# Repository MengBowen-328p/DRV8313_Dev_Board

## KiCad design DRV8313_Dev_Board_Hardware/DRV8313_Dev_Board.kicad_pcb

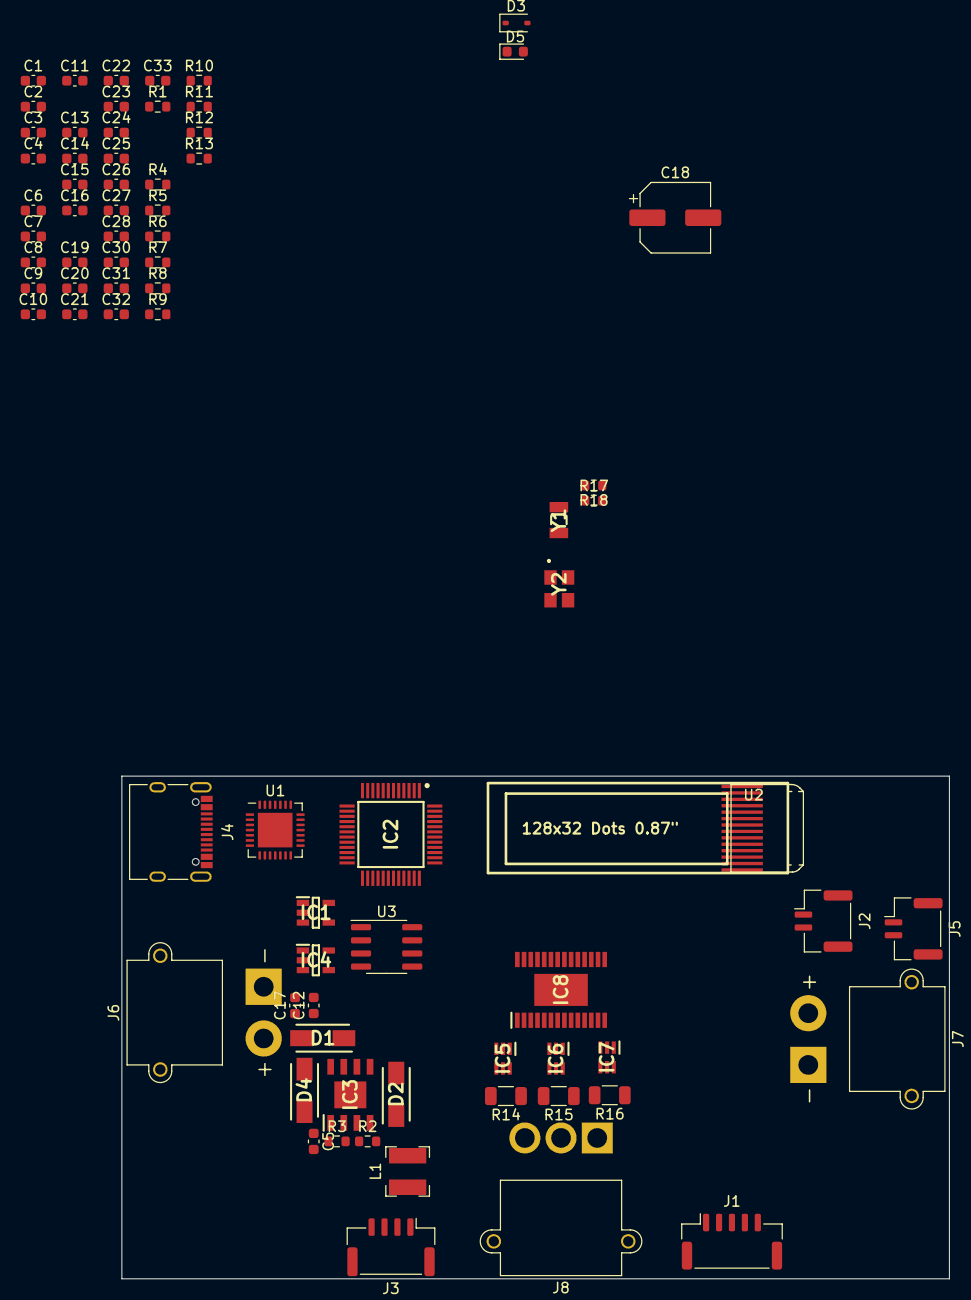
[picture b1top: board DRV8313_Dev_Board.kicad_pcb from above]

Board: 2 copper layers, 80.0 x 48.6 mm, 77 parts (0 on the bottom side), 65 nets, no tracks yet.

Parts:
C1, C5, C9, C10, C11, C13, C23, C26, C31: 0.1uF; C_0603_1608Metric
C2, C7, C15, C19, C27, C28: 1uF; C_0603_1608Metric
C3, C6, C16: 47pF; C_0603_1608Metric
C4: 47pf; C_0603_1608Metric
C8, C20: 0.01uF; C_0603_1608Metric
C12, C14, C17, C21, C22, C25: 4.7uF; C_0603_1608Metric
C18: 470uF; CP_Elec_6.3x5.7
C24: 2.2uF; C_0603_1608Metric
C30: 0.47uF; C_0603_1608Metric
C32: 0.01uF/60V; C_0603_1608Metric
C33: 0.1uF/16V; C_0603_1608Metric
D1, D2, D4: SS54; DIOM5126X245N
D3: 1N4148WS; D_SOD-323
D5: FAULT; LED_0603_1608Metric
IC1, IC4: LP2992IM5-3.3; SOT95P280X145-5N
IC2: STM32F103C8T6TR; QFP50P900X900X160-48N
IC3: TPS5450DDAR; SOIC127P600X170-9N
IC5, IC6, IC7: INA199A1DCKR; SOT65P210X110-6N
IC8: DRV8313PWP; SOP65P640X120-29N
J1: HALL_Sensor_Port; JST_GH_SM05B-GHS-TB_1x05-1MP_P1.25mm_Horizontal
J2: CAN_BUS_Port_IN; JST_GH_BM02B-GHS-TBT_1x02-1MP_P1.25mm_Vertical
J3: AS5600_Port; JST_GH_BM04B-GHS-TBT_1x04-1MP_P1.25mm_Vertical
J4: USB_C_Receptacle; USB_C_Receptacle_XKB_U262-16XN-4BVC11
J5: CAN_BUS_Port_OUT; JST_GH_BM02B-GHS-TBT_1x02-1MP_P1.25mm_Vertical
J6: DC_IN; AMASS_XT30PW-M_1x02_P2.50mm_Horizontal
J7: DC_OUT; AMASS_XT30PW-M_1x02_P2.50mm_Horizontal
J8: Conn_01x03_Socket; AMASS_MR30PW-M_1x03_P3.50mm_Horizontal
L1: 15uH; L_Bourns-SRN4018
R1, R2, R4: 10K; R_0603_1608Metric
R3: 3.16K; R_0603_1608Metric
R5, R6, R7, R8, R10: 4.7K; R_0603_1608Metric
R9: 560K; R_0603_1608Metric
R11, R12: 5K1; R_0603_1608Metric
R13: 4.99K; R_0603_1608Metric
R14, R15, R16: 500mR; R_1206_3216Metric
R17: 120R; R_0603_1608Metric
R18: 0R; R_0603_1608Metric
U1: CP2102N-Axx-xQFN28; QFN-28-1EP_5x5mm_P0.5mm_EP3.35x3.35mm
U2: 中景园_0.87寸OLED; 中景园0.87寸OLED
U3: SN65HVD232; SOIC-8_3.9x4.9mm_P1.27mm
Y1: 32.768KHZ_YST310S; 32768KHZYST310S
Y2: YSX321SL

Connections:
+3.3V: C7.1, C9.1, C10.1, C11.1, C13.1, C22.2, C23.2, C31.2, IC1.5 (OUT), IC2.1 (VBAT), IC2.9 (VDDA), IC2.24 (VDD_1), IC2.36 (VDD_2), IC2.48 (VDD_3), R1.2, R7.1, R8.1, R10.1, U2.5 (VBAT), U2.8 (VDD), U3.3 (VCC)
+5V: C2.1, C14.1, C15.1, C18.1, D3.1 (K), IC1.1 (IN), IC1.3 (ON/~OFF), IC4.1 (IN), IC4.3 (ON/~OFF), L1.2, R2.2, R4.2, U1.7 (VREGIN), U1.8 (VBUS)
/AS5600_SCL: J3.2, R8.2
/AS5600_SDA: J3.3, R10.2
/CAN_DN: J2.2, J5.2, R18.1, U3.6 (CANL)
/CAN_DP: J2.1, J5.1, R17.2, U3.7 (CANH)
/EN1: IC2.26 (PB13), IC8.26 (EN1)
/EN2: IC2.27 (PB14), IC8.24 (EN2)
/EN3: IC2.28 (PB15), IC8.22 (EN3)
/FAULT: D5.1 (K), IC2.39 (PB3), IC8.18 (NFAULT)
/IN1: IC2.29 (PA8), IC8.27 (IN1)
/IN2: IC2.30 (PA9), IC8.25 (IN2)
/IN3: IC2.31 (PA10), IC8.23 (IN3)
/ISense_U: IC2.12 (PA2), IC5.6 (OUT)
/ISense_V: IC2.11 (PA1), IC6.6 (OUT)
/ISense_W: IC2.10 (PA0-WKUP), IC7.6 (OUT)
/MCU_CAN_DN: IC2.32 (PA11), U3.4 (R)
/MCU_CAN_DP: IC2.33 (PA12), U3.1 (D)
/Motor0_U: IC5.4 (IN+), J8.3, R14.2
/Motor0_V: IC6.4 (IN+), J8.2, R15.2
/Motor0_W: IC7.4 (IN+), J8.1, R16.2
/OLED_SCL: IC2.45 (PB8), R5.2, U2.10 (SCL)
/OLED_SDA: IC2.46 (PB9), R6.2, U2.11 (SDA)
/OSC32_IN: C3.1, IC2.3 (PC14-OSC32_IN), Y1.2 (CRYSTAL_2)
/OSC32_OUT: C4.1, IC2.4 (PC15-OSC32_OUT), Y1.1
/OSC_IN: C6.1, IC2.5 (PD0-OSC_IN), Y2.1 (CRYSTAL_1)
/OSC_OUT: C16.2, IC2.6 (PD1-OSC_OUT), Y2.3 (CRYSTAL_2)
/OUT1: IC5.5 (IN-), IC8.5 (OUT1), R14.1
/OUT2: IC6.5 (IN-), IC8.8 (OUT2), R15.1
/OUT3: IC7.5 (IN-), IC8.9 (OUT3), R16.1
/RESET: IC2.41 (PB5), IC8.16 (NRESET)
/SLEEP: IC2.40 (PB4), IC8.17 (NSLEEP)
/USART1_RXD: IC2.43 (PB7), U1.26 (TXD)
/USART1_TXD: IC2.42 (PB6), U1.25 (RXD)
/USB_DN: J4.A7 (D-), J4.B7 (D-), U1.5 (D-)
/USB_DP: J4.A6 (D+), J4.B6 (D+), U1.4 (D+)
/V3P3_OUT: C30.2, IC5.3 (V+), IC6.3 (V+), IC7.3 (V+), IC8.15 (V3P3), R13.1
/VCC_OLED: R5.1, R6.1
/VCC_Sensor: C19.1, IC4.5 (OUT), J1.1, J3.1
GND: C1.2, C2.2, C3.2, C4.2, C6.2, C7.2, C8.2, C9.2, C10.2, C11.2, C12.2, C13.2, C14.2, C15.2, C16.1, C17.2, C18.2, C19.2, C20.2, C21.1, C22.1, C23.1, C24.1, C25.1, C26.1, C30.1, C31.1, D2.2 (A), D4.2 (A), IC1.2 (GND), IC2.8 (VSSA), IC2.23 (VSS_1), IC2.35 (VSS_2), IC2.47 (VSS_3), IC3.6 (GND), IC3.9 (EP), IC4.2 (GND), IC5.1 (REF), IC5.2 (GND), IC6.1 (REF), IC6.2 (GND), IC7.1 (REF), IC7.2 (GND), IC8.6 (PGND1), IC8.7 (PGND2), IC8.10 (PGND3), IC8.14 (GND_1), IC8.20 (GND_2), IC8.28 (GND_3), IC8.29 (POWERPAD), J1.5, J3.4, J4.A1 (GND), J4.A12 (GND), J4.B1 (GND), J4.B12 (GND), J4.S1 (SHIELD), J6.1, J7.1, R3.1, R9.1, R11.2, R12.2, U1.3 (GND), U1.29 (GND), U2.7 (VSS), U3.2 (GND), Y2.2 (GND_1), Y2.4 (GND_2)
unnamed: D1.1 (K), IC3.7 (VIN)
unnamed: C5.1, D2.1 (K), IC3.8 (PH), L1.1
unnamed: D3.2 (A), J4.A4 (VBUS), J4.A9 (VBUS), J4.B4 (VBUS), J4.B9 (VBUS)
unnamed: D5.2 (A), R13.2
unnamed: C8.1, IC1.4 (BYPASS)
unnamed: C1.1, IC2.7 (NRST), R1.1
unnamed: C5.2, IC3.1 (BOOT)
unnamed: IC3.4 (VSENSE), R2.1, R3.2
unnamed: C20.1, IC4.4 (BYPASS)
unnamed: C32.1, IC8.2 (CPH)
unnamed: C32.2, IC8.1 (CPL)
unnamed: C33.2, IC8.3 (VCP)
unnamed: J4.A5 (CC1), R11.1
unnamed: J4.B5 (CC2), R12.1
unnamed: R17.1, R18.2
unnamed: R4.1, U1.9 (~RST)
unnamed: R9.2, U2.12 (IREF)
unnamed: C21.2, R7.2, U2.9 (RES#)
unnamed: C25.2, C26.2, U2.14 (VCC)
unnamed: C24.2, U2.13 (VCOMH)
unnamed: C28.1, U2.4 (c1n)
unnamed: C28.2, U2.3 (c1p)
unnamed: C27.1, U2.2 (c2n)
unnamed: C27.2, U2.1 (c2p)
VCC: C12.1, C17.1, C33.1, D1.2 (A), D4.1 (K), IC8.4 (VM_1), IC8.11 (VM_2), J6.2, J7.2

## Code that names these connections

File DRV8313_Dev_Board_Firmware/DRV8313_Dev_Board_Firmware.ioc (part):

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Mcu.Name=STM32F103C(8-B)Tx
Mcu.Package=LQFP48
Mcu.UserName=STM32F103C8Tx
PA0-WKUP.Signal=ADCx_IN0
PA1.Signal=ADCx_IN1
PA10.Signal=S_TIM1_CH3
PA11.Mode=CAN_Activate
PA11.Signal=CAN_RX
PA12.Mode=CAN_Activate
PA12.Signal=CAN_TX
PA13.Mode=Serial_Wire
PA13.Signal=SYS_JTMS-SWDIO
PA14.Mode=Serial_Wire
PA14.Signal=SYS_JTCK-SWCLK
PA2.Signal=ADCx_IN2
PA3.Signal=ADCx_IN3
PA8.Signal=S_TIM1_CH1
PA9.Signal=S_TIM1_CH2
PB10.Mode=I2C
PB10.Signal=I2C2_SCL
PB11.Mode=I2C
PB11.Signal=I2C2_SDA
PB13.GPIOParameters=GPIO_Label
PB13.GPIO_Label=DRV_EN1
PB13.Signal=GPIO_Output
PB14.GPIOParameters=GPIO_Label
PB14.GPIO_Label=DRV_EN2
PB14.Signal=GPIO_Output
PB15.GPIOParameters=GPIO_Label
PB15.GPIO_Label=DRV_EN3
PB15.Signal=GPIO_Output
PB3.GPIOParameters=GPIO_Label
PB3.GPIO_Label=DRV_FAULT
PB3.Signal=GPIO_Input
PB4.GPIOParameters=GPIO_Label
PB4.GPIO_Label=DRV_SLEEP
PB4.Signal=GPIO_Output
PB5.GPIOParameters=GPIO_Label
PB5.GPIO_Label=DRV_RESET
PB5.Signal=GPIO_Output
PB6.Mode=Asynchronous
PB6.Signal=USART1_TX
PB7.Mode=Asynchronous
PB7.Signal=USART1_RX
PB8.Mode=I2C
PB8.Signal=I2C1_SCL
PB9.Mode=I2C
PB9.Signal=I2C1_SDA
PC14-OSC32_IN.Mode=LSE-External-Oscillator
PC14-OSC32_IN.Signal=RCC_OSC32_IN
PC15-OSC32_OUT.Mode=LSE-External-Oscillator
PC15-OSC32_OUT.Signal=RCC_OSC32_OUT
PD0-OSC_IN.Mode=HSE-External-Oscillator
PD0-OSC_IN.Signal=RCC_OSC_IN
PD1-OSC_OUT.Mode=HSE-External-Oscillator
PD1-OSC_OUT.Signal=RCC_OSC_OUT
board=custom

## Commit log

2023-11-26 Init Repo
2023-11-27 Updata SCH Alpha0.2
2023-11-28 Updata SCH Alpha0.3
